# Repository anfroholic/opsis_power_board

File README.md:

# opsis_power_board
power distribution board for Carl's Opsis video mixer board thing

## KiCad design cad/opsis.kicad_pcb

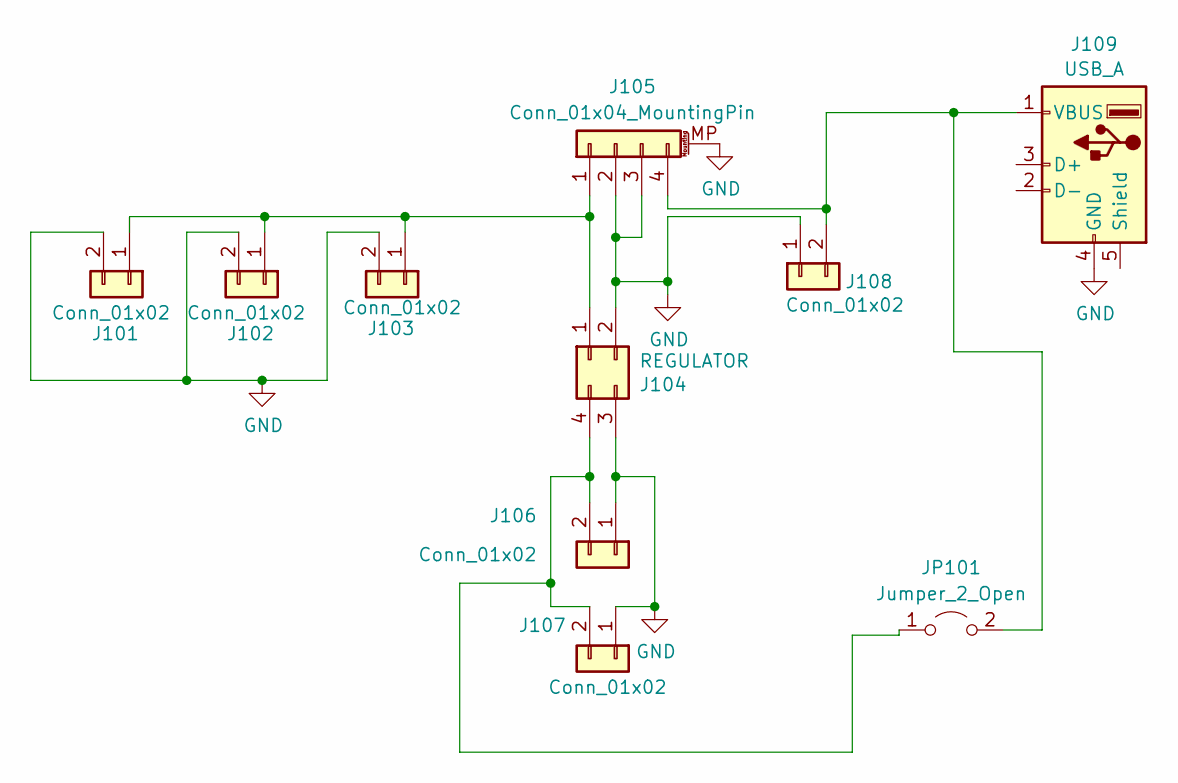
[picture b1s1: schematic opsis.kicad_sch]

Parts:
J101: Conn_01x02; PhoenixContact_MC_1,5_2-G-3.81_1x02_P3.81mm_Horizontal
J102, J103: Conn_01x02; JST_XH_S2B-XH-A_1x02_P2.50mm_Horizontal
J104: REGULATOR; LM2596_DC-DC
J105: Conn_01x04_MountingPin; Molex_HDD_POWER_CONN
J106, J107, J108: Conn_01x02; Molex_KK-254_AE-6410-02A_1x02_P2.54mm_Vertical
J109: USB_A; USB_A_CONNFLY_DS1095-WNR0
JP101: Jumper_2_Open; SolderJumper-2_P1.3mm_Open_RoundedPad1.0x1.5mm

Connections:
GND: J101.2, J102.2, J103.2, J104.2, J104.3, J105.2, J105.3, J105.MP (MountPin), J106.1, J107.1, J108.1, J109.4 (GND)
unnamed: J101.1, J102.1, J103.1, J104.1, J105.1
unnamed: J104.4, J106.2, J107.2, JP101.1 (A)
unnamed: J105.4, J108.2, J109.1 (VBUS), JP101.2 (B)

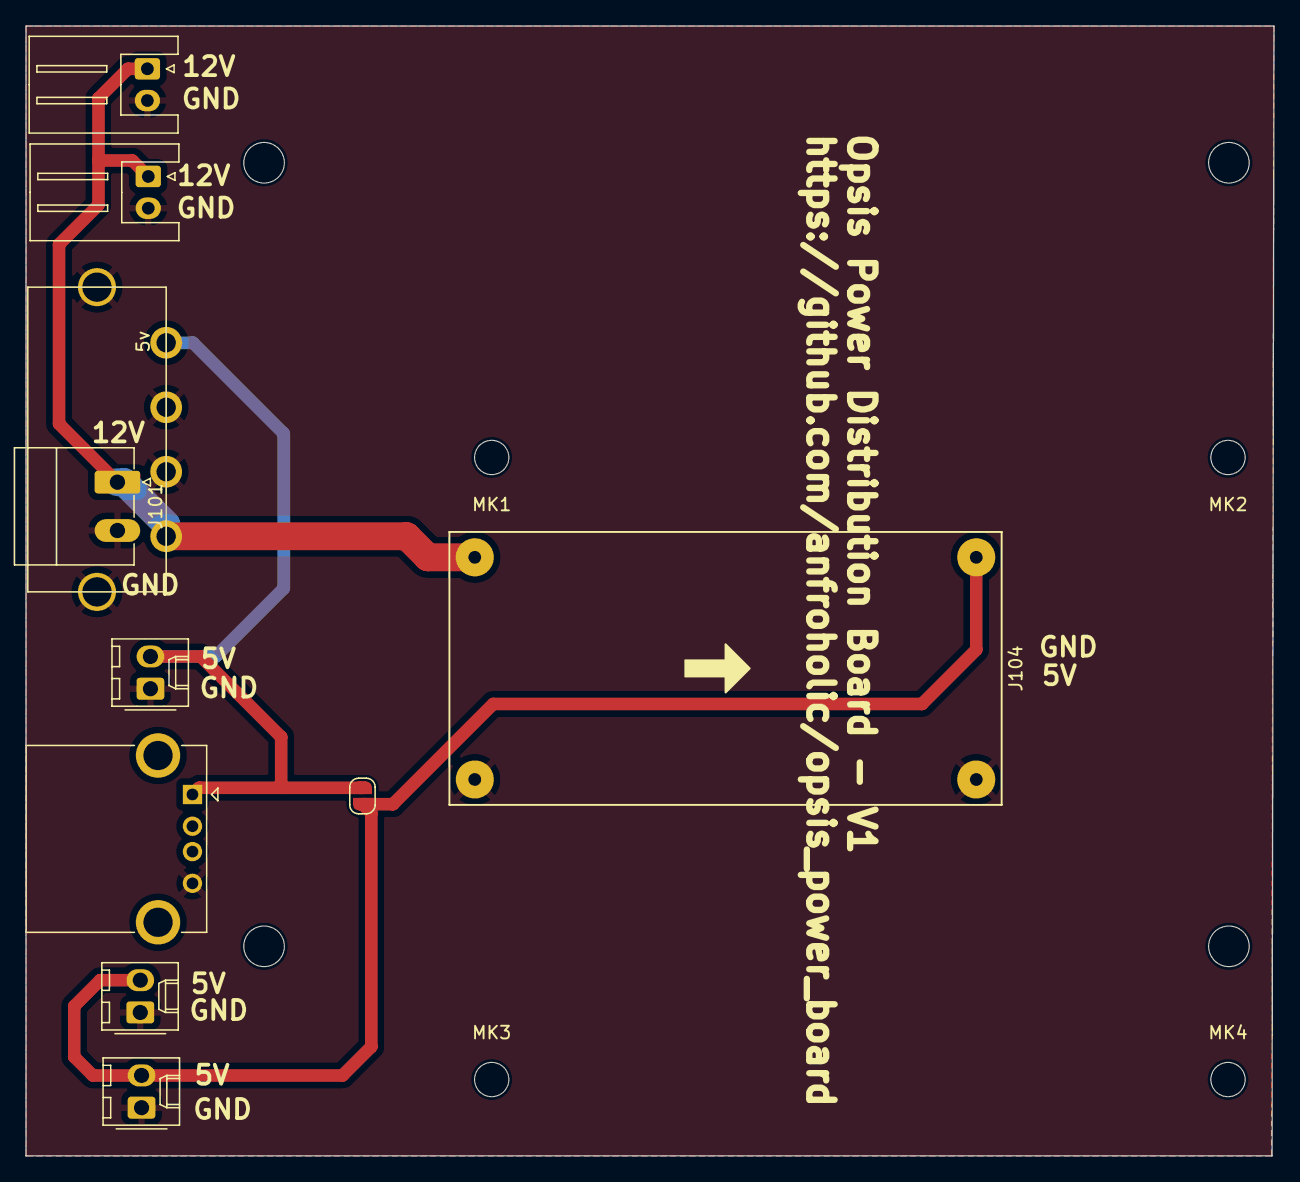
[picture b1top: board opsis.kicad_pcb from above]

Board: 2 copper layers, 98.3 x 89.0 mm, 18 parts (0 on the bottom side), 4 nets.

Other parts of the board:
H101, H102, H103, H104: MountingHole; MountingHole_3.2mm_M3_DIN965
MK1, MK2, MK3, MK4: M2.5; MountingHole_2.7mm_M2.5

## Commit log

2024-06-17 init
2024-06-25 initial rev made
